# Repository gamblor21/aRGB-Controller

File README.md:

# aRGB-Controller
PCB with nRF52840 and 5V logic level shifting to control aRGB case lights

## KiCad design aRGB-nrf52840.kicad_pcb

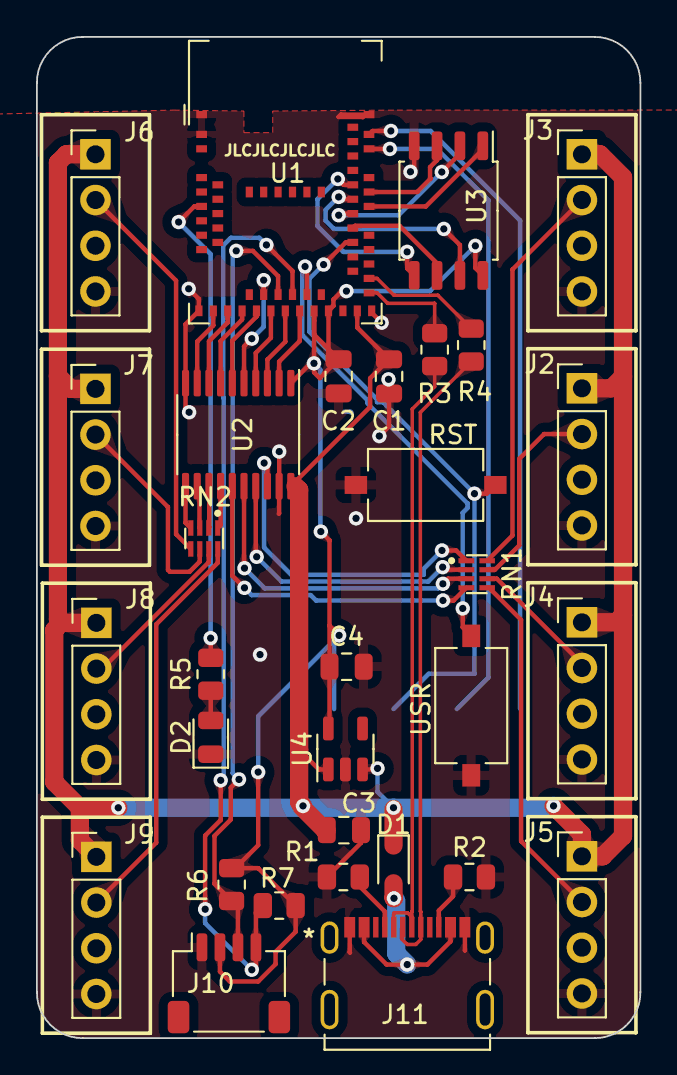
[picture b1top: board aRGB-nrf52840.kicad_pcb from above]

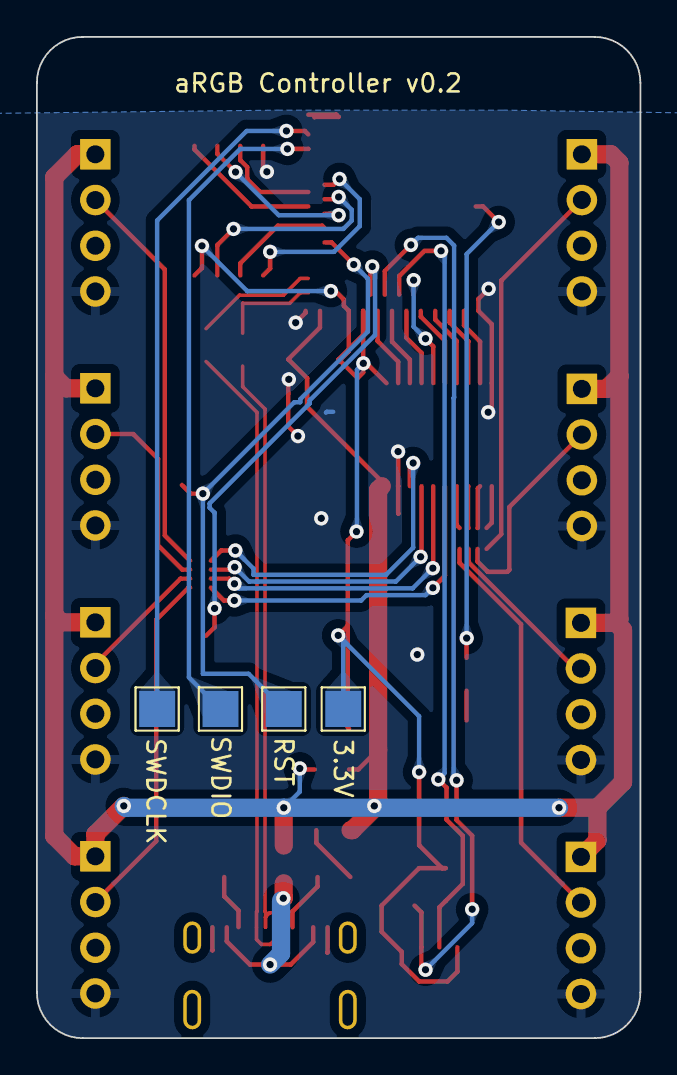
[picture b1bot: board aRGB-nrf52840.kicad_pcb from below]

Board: 2 copper layers, 33.5 x 55.6 mm, 35 parts (4 on the bottom side), 48 nets.

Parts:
3.3V: TP 3.3V; TestPoint_Pad_2.0x2.0mm
C1, C2: 10uF; C_0805_2012Metric
C3, C4: 1uF; C_0805_2012Metric
D1: D_Schottky; D_SOD-323
D2: LED; LED_0805_2012Metric
J2: aRGB Socket 1; PinHeader_1x04_P2.54mm_Vertical
J3: aRGB Socket 0; PinHeader_1x04_P2.54mm_Vertical
J4: aRGB Socket 2; PinHeader_1x04_P2.54mm_Vertical
J5: aRGB Socket 3; PinHeader_1x04_P2.54mm_Vertical
J6: aRGB Socket 4; PinHeader_1x04_P2.54mm_Vertical
J7: aRGB Socket 5; PinHeader_1x04_P2.54mm_Vertical
J8: aRGB Socket 6; PinHeader_1x04_P2.54mm_Vertical
J9: aRGB Socket 7; PinHeader_1x04_P2.54mm_Vertical
J10: Conn_01x04; JST_SH_SM04B-SRSS-TB_1x04-1MP_P1.00mm_Horizontal
J11: 2171790001
R1, R2: 5.1K; R_0805_2012Metric
R3, R4: 22; R_0805_2012Metric
R5: 1K; R_0805_2012Metric
R6, R7: 10K; R_0805_2012Metric
RN1, RN2: 100; RESCAV50P200X100X55-8N
RST: Reset switch; SW_Tactile_SPST_NO_Straight_CK_PTS636Sx25SMTRLFS
RST#2: TP RESET; TestPoint_Pad_2.0x2.0mm
SWDCLK: TP SWDCLK; TestPoint_Pad_2.0x2.0mm
SWDIO: TP SWDIO; TestPoint_Pad_2.0x2.0mm
U1: MDBT50Q-1MV2; Raytac_MDBT50Q
U2: 74AHCT245; TSSOP-20_4.4x6.5mm_P0.65mm
U3: GD25Q16C; SOIC-8_5.23x5.23mm_P1.27mm
U4: AP2112K-3.3; SOT-23-5
USR: User Button; SW_Tactile_SPST_NO_Straight_CK_PTS636Sx25SMTRLFS

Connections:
3.3V: 3.3V.1, C2.2, C4.1, J10.2, R6.2, R7.1, U1.28 (VDD), U1.30 (VDDH), U2.1 (DIR), U3.8 (VCC), U4.5 (VOUT)
5V: C1.2, C3.1, D1.1 (K), J2.1, J3.1, J4.1, J5.1, J6.1, J7.1, J8.1, J9.1, U1.32 (VBUS), U2.20 (Vcc), U4.1 (VIN), U4.3 (EN)
D+: R4.1, U1.35 (D+)
D-: R3.1, U1.34 (D-)
DN: J11.A7 (DN1), J11.B7 (DN2), R3.2
DP: J11.A6 (DP1), J11.B6 (DP2), R4.2
GND: C1.1, C2.1, C3.2, C4.2, D2.1 (K), J2.4, J3.4, J4.4, J5.4, J6.4, J7.4, J8.4, J9.4, J10.1, J11.A1/B12 (GND), J11.B1/A12 (GND), R1.1, R2.2, RST.1, U1.1 (GND), U1.2 (GND), U1.15 (GND), U1.33 (GND), U1.55 (GND), U2.10 (GND), U2.19 (~OE), U3.4 (VSS), U4.2 (GND), USR.1
LED: R5.2, U1.8 (P1.15)
unnamed: D2.2 (A), R5.1
unnamed: J11.A5 (CC1), R1.2
unnamed: J11.B5 (CC2), R2.1
unnamed: RN1.1 (R1.1), U2.18 (B0)
unnamed: RN1.2 (R2.1), U2.17 (B1)
unnamed: RN1.3 (R3.1), U2.16 (B2)
unnamed: RN1.4 (R4.1), U2.15 (B3)
unnamed: RN2.1 (R1.1), U2.14 (B4)
unnamed: RN2.2 (R2.1), U2.13 (B5)
unnamed: RN2.3 (R3.1), U2.12 (B6)
unnamed: RN2.4 (R4.1), U2.11 (B7)
QSPI_CS: U1.44 (P0.20), U3.1 (CS)
QSPI_DATA0: U1.47 (TRACEDATA0/P1.00), U3.5 (SI(IO0))
QSPI_DATA1: U1.43 (P0.21), U3.2 (SO(IO1))
QSPI_DATA2: U1.46 (P0.22), U3.3 (WP#(IO2))
QSPI_DATA3: U1.45 (P0.23), U3.7 (HOLD#(IO3))
QSPI_SCK: U1.42 (P0.19), U3.6 (SCLK)
RESET: RST.2, RST#2.1, U1.40 (~RESET/P0.18)
SCL: J10.4, R7.2, U1.25 (P1.08)
SDA: J10.3, R6.1, U1.23 (TRACECLK/P0.07)
SWDCLK: SWDCLK.1, U1.53 (SWDCLK)
SWDIO: SWDIO.1, U1.51 (SWDIO)
USER_BTN: U1.27 (TRACEDATA2/P0.11), USR.2
VBUS: D1.2 (A), J11.A4/B9 (VBUS), J11.B4/A9 (VBUS)
aRGB0: U1.26 (TRACEDATA3/P1.09), U2.2 (A0)
aRGB1: U1.24 (P0.08), U2.3 (A1)
aRGB2: U1.22 (P0.06), U2.4 (A2)
aRGB3: U1.21 (P0.05/AIN3), U2.5 (A3)
aRGB4: U1.16 (P0.27), U2.9 (A7)
aRGB5: U1.17 (XL1/P0.00), U2.8 (A6)
aRGB6: U1.18 (XL2/P0.01), U2.7 (A5)
aRGB7: U1.20 (P0.04/AIN2), U2.6 (A4)
aRGB_5V_0: J3.2, RN1.8 (R1.2)
aRGB_5V_1: J2.2, RN1.7 (R2.2)
aRGB_5V_2: J4.2, RN1.6 (R3.2)
aRGB_5V_3: J5.2, RN1.5 (R4.2)
aRGB_5V_4: J6.2, RN2.5 (R4.2)
aRGB_5V_5: J7.2, RN2.6 (R3.2)
aRGB_5V_6: J8.2, RN2.7 (R2.2)
aRGB_5V_7: J9.2, RN2.8 (R1.2)

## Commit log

2023-05-01 Create hardware-LICENSE

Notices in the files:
parts and their libraries:
Copyright 2021 Accelerated Designs. All rights reserved.
